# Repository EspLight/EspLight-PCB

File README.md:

# EspLight-PCB

License: CC BY-SA 3.0

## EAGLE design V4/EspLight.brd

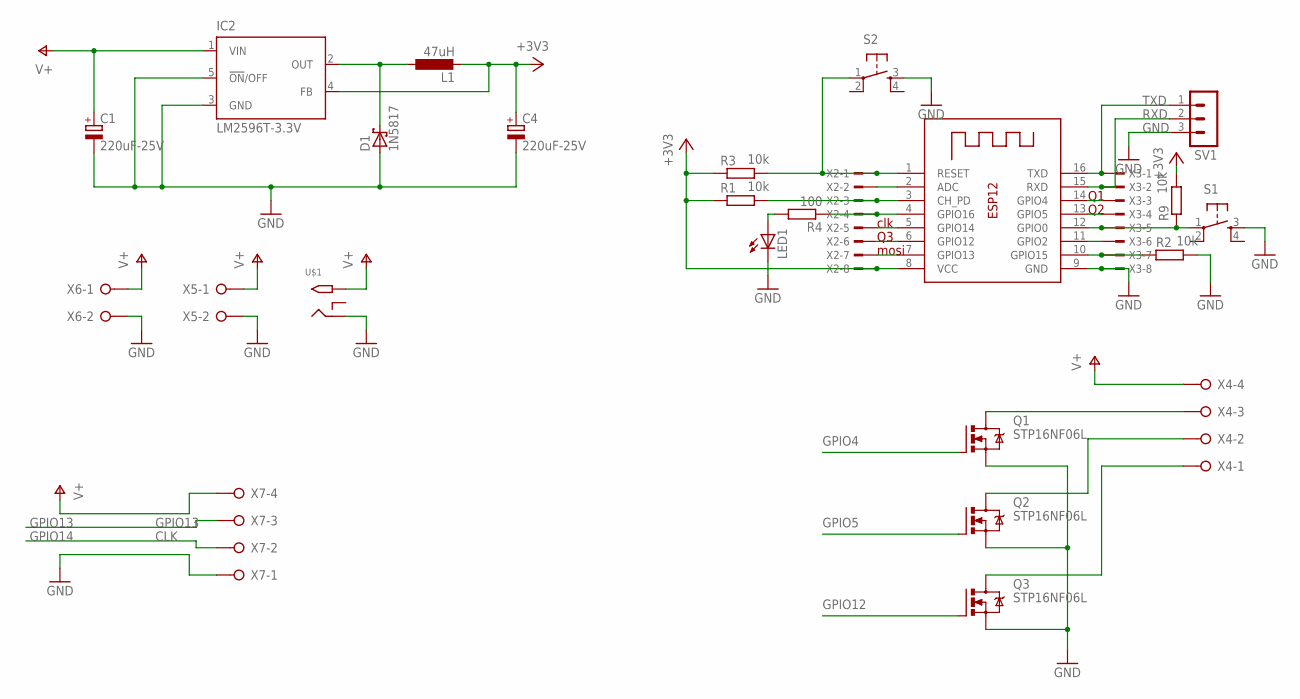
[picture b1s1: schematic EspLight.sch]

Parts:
C1, C4: 220uF-25V; E2,5-7
D1: 1N5817; DO41-7.6
IC2: LM2596T-3.3V; T05D
L1: 47uH; 6000-XXXX-RC
LED1: LED5MM
Q1, Q2, Q3: STP16NF06L; TO220BV
R1, R2, R3, R9: 10k; 0207/10
R4: 100; 0207/10
S1, S2: TAC_SWITCHPTH; TACTILE-PTH
SV1: MA03-1
U$1: 2.1MMJACKTHM; PJ-102A
X1: ESP-12
X2, X3: TSW-108-02-S-S
X4, X7: W237-04P; W237-4P
X5, X6: W237-02P; W237-132

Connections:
+3V3: C4.+, IC2.4 (FB), L1.2, R1.1, R3.1, R9.2, X1.8 (VCC), X2.8
GND: C1.-, C4.-, D1.A, IC2.3 (GND), IC2.5 (!ON!/OFF), LED1.K (C), Q1.S, Q2.S, Q3.S, R2.2, S1.3, S2.3, SV1.3, U$1.RING, X1.9 (GND), X3.8, X5.2, X6.2, X7.1
GPIO2: X1.11 (GPIO2), X3.6
GPIO4: Q1.G, X1.14 (GPIO4), X3.3
GPIO5: Q2.G, X1.13 (GPIO5), X3.4
GPIO12: Q3.G, X1.6 (GPIO12), X2.6
GPIO13: X1.7 (GPIO13), X2.7, X7.3
GPIO14: X1.5 (GPIO14), X2.5, X7.2
unnamed: R3.2, S2.1, X1.1 (RESET), X2.1
unnamed: R1.2, X1.3 (CH_PD), X2.3
unnamed: R2.1, X1.10 (GPIO15), X3.7
unnamed: R4.1, X1.4 (GPIO16), X2.4
unnamed: R9.1, S1.1, X1.12 (GPIO0), X3.5
unnamed: X1.2 (ADC), X2.2
unnamed: LED1.A, R4.2
unnamed: D1.C, IC2.2 (OUT), L1.1
unnamed: Q1.D, X4.3
unnamed: Q2.D, X4.2
unnamed: Q3.D, X4.1
RXD: SV1.2, X1.15 (RXD), X3.2
TXD: SV1.1, X1.16 (TXD), X3.1
V+: C1.+, IC2.1 (VIN), U$1.TIP, X4.4, X5.1, X6.1, X7.4

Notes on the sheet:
clk
mosi
CLK

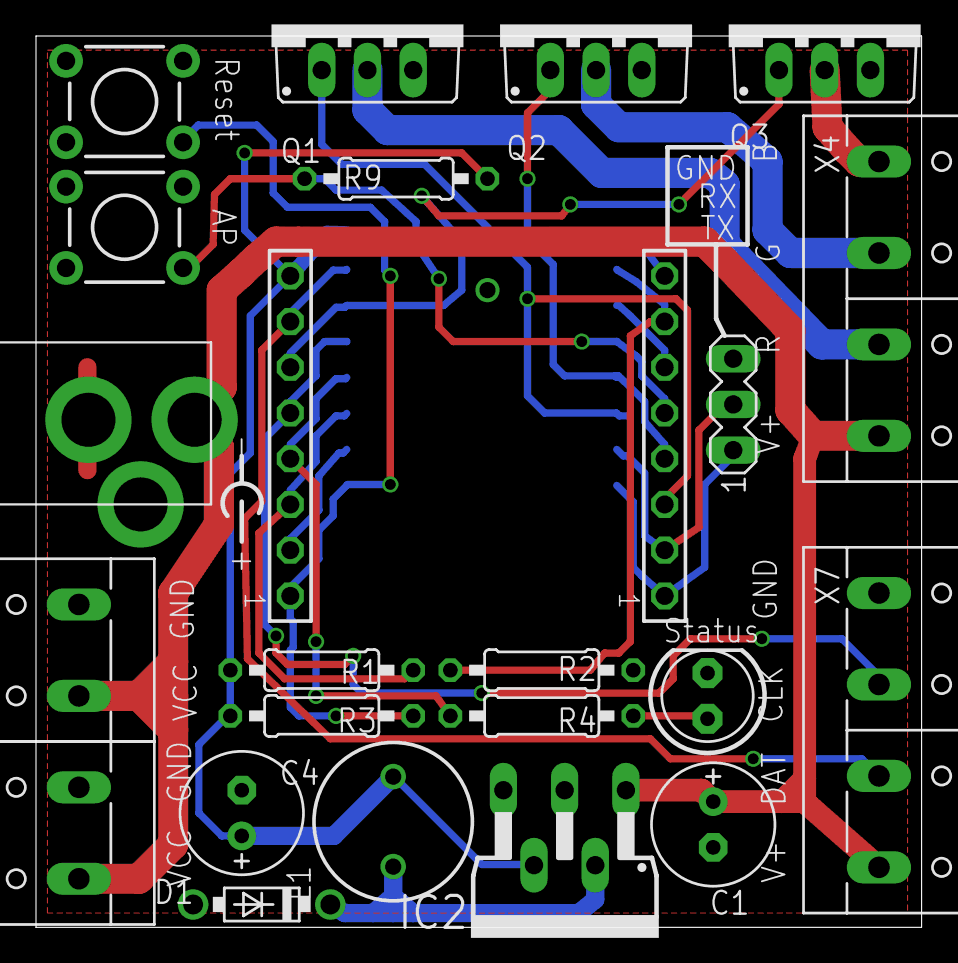
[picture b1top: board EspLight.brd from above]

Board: 2 copper layers, 49.2 x 49.5 mm, 25 parts (1 on the bottom side), 22 nets.

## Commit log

2015-11-22 add gitignore
2015-11-22 add V4 PCB
2016-01-17 change picture to a good one

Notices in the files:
parts and their libraries:
SparkFun-Retired: Licensing:Creative Commons ShareAlike 4.0 International - https://creativecommons.org/licenses/by-sa/4.0
